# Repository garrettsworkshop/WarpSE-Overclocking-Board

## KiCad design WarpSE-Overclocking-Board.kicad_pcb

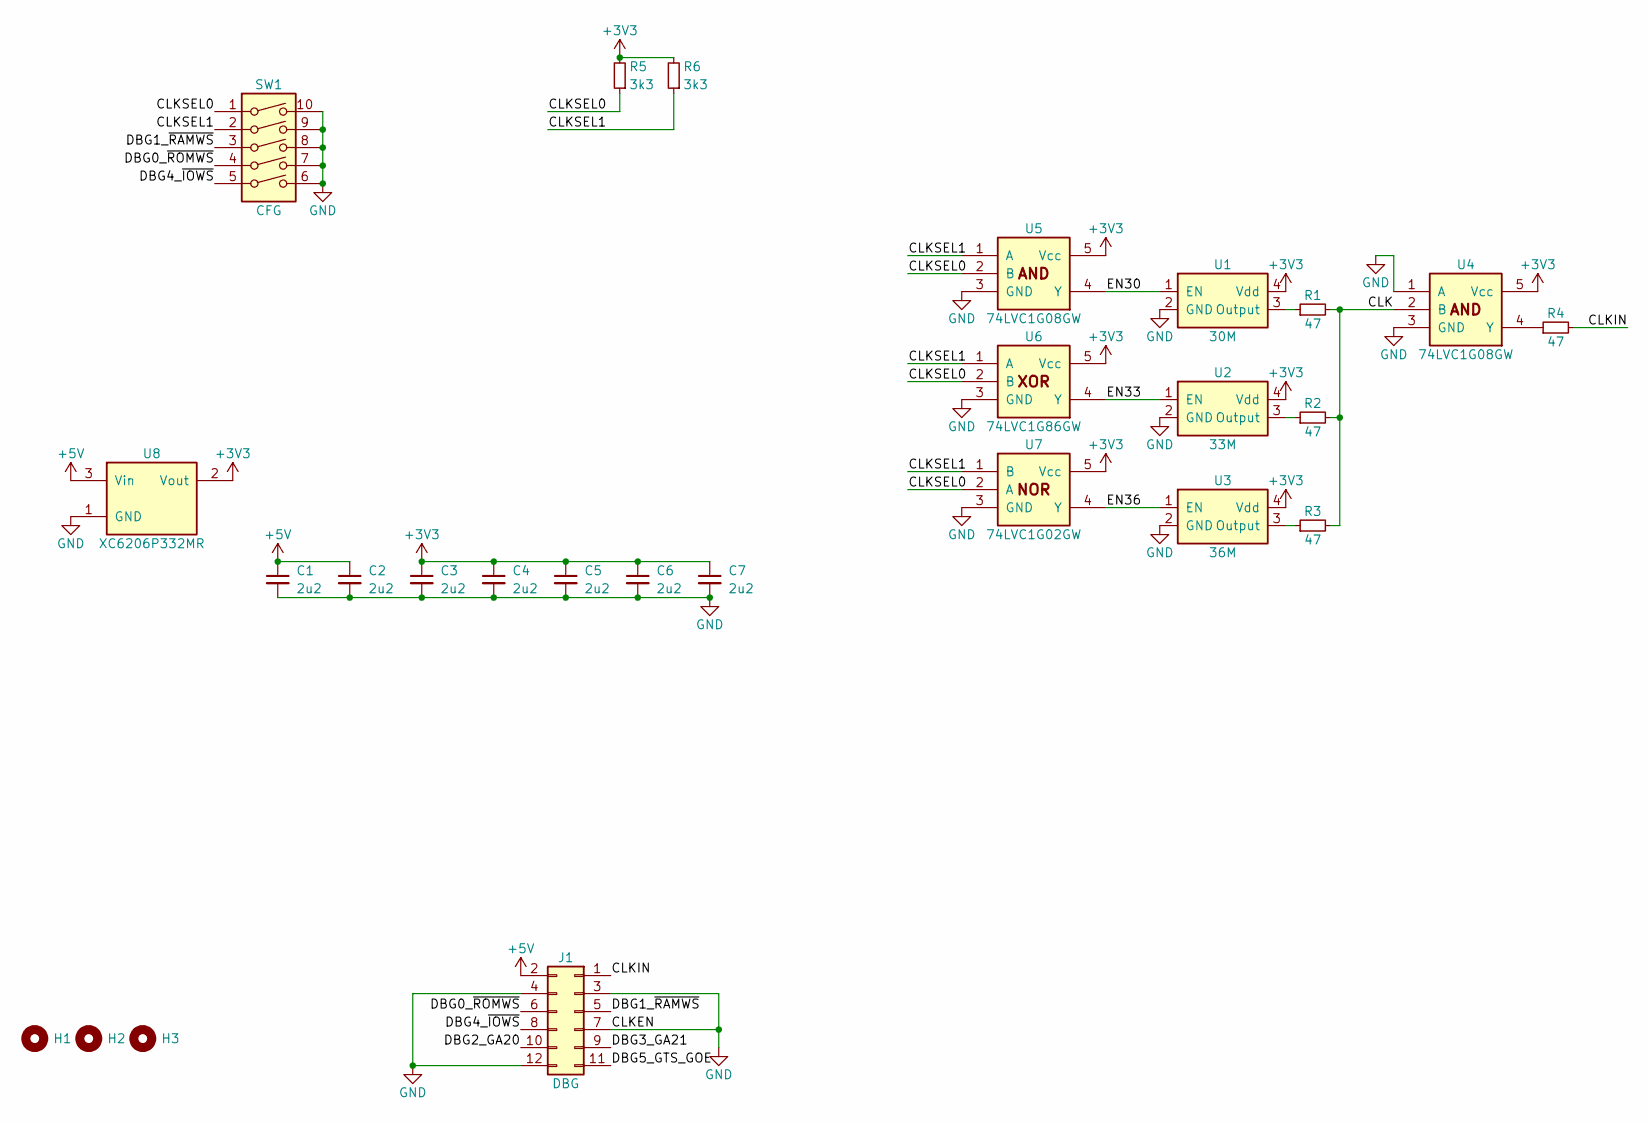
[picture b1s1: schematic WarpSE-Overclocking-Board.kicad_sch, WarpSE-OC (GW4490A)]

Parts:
C1, C2, C3, C4, C5, C6, C7: 2u2; C_0603; LCSC Part c23630
H1, H2, H3: PasteHole_1.152mm_NPTH
J1: DBG; PinHeader_2x06_P2.00mm_Vertical
R1, R2, R3, R4: 47; R_0603; LCSC Part C23182
R5, R6: 3k3; R_0603; LCSC Part C22978
SW1: CFG; SW_DIP_SPSTx05_Slide_DSHP05TS_P1.27mm; LCSC Part C2884836
U1: 30M; Crystal_SMD_3225-4Pin_3.2x2.5mm; LCSC Part C5179973
U2: 33M; Crystal_SMD_3225-4Pin_3.2x2.5mm; LCSC Part C5179975
U3: 36M; Crystal_SMD_3225-4Pin_3.2x2.5mm; LCSC Part C5179977
U4, U5: 74LVC1G08GW; SOT-353; LCSC Part C12512
U6: 74LVC1G86GW; SOT-353; LCSC Part C52350
U7: 74LVC1G02GW; SOT-353; LCSC Part C546692
U8: XC6206P332MR; SOT-23; LCSC Part C5446

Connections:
+3V3: C3.1, C4.1, C5.1, C6.1, C7.1, R5.2, R6.2, U1.4 (Vdd), U2.4 (Vdd), U3.4 (Vdd), U4.5 (Vcc), U5.5 (Vcc), U6.5 (Vcc), U7.5 (Vcc), U8.2 (Vout)
+5V: C1.1, C2.1, J1.2, U8.3 (Vin)
/CLK: R1.2, R2.2, R3.2, U4.2 (B)
/CLKIN: J1.1, R4.2
/CLKSEL0: R5.1, SW1.1, U5.2 (B), U6.2 (B), U7.2 (A)
/CLKSEL1: R6.1, SW1.2, U5.1 (A), U6.1 (A), U7.1 (B)
/DBG0_~ROMWS: J1.6, SW1.4
/DBG1_~RAMWS: J1.5, SW1.3
/DBG2_GA20: J1.10
/DBG3_GA21: J1.9
/DBG4_~IOWS: J1.8, SW1.5
/DBG5_GTS_GOE: J1.11
/EN30: U1.1 (EN), U5.4 (Y)
/EN33: U2.1 (EN), U6.4 (Y)
/EN36: U3.1 (EN), U7.4 (Y)
GND: C1.2, C2.2, C3.2, C4.2, C5.2, C6.2, C7.2, J1.3, J1.4, J1.7, J1.12, SW1.6, SW1.7, SW1.8, SW1.9, SW1.10, U1.2 (GND), U2.2 (GND), U3.2 (GND), U4.1 (A), U4.3 (GND), U5.3 (GND), U6.3 (GND), U7.3 (GND), U8.1 (GND)
unnamed: R1.1, U1.3 (Output)
unnamed: R2.1, U2.3 (Output)
unnamed: R3.1, U3.3 (Output)
unnamed: R4.1, U4.4 (Y)

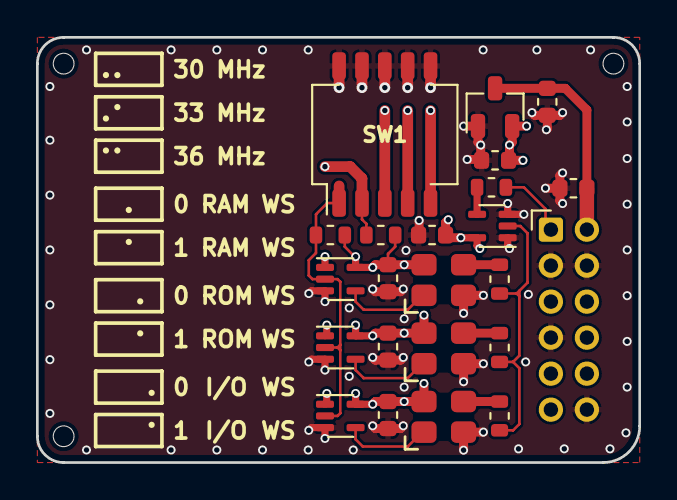
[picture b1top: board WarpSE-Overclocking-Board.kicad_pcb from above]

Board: 4 copper layers, 33.5 x 23.6 mm, 26 parts (0 on the bottom side), 17 nets.

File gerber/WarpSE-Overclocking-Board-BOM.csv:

"Reference","Quantity","Value","Footprint","LCSC Part","DNP"
"C1, C2, C3, C4, C5, C6, C7","7","2u2","stdpads:C_0603","c23630",""
"H1, H2, H3","3","~","stdpads:PasteHole_1.152mm_NPTH","",""
"J1","1","DBG","stdpads:PinHeader_2x06_P2.00mm_Vertical","",""
"R1, R2, R3, R4","4","47","stdpads:R_0603","C23182",""
"R5, R6","2","3k3","stdpads:R_0603","C22978",""
"SW1","1","CFG","stdpads:SW_DIP_SPSTx05_Slide_DSHP05TS_P1.27mm","C2884836",""
"U1","1","30M","stdpads:Crystal_SMD_3225-4Pin_3.2x2.5mm","C5179973",""
"U2","1","33M","stdpads:Crystal_SMD_3225-4Pin_3.2x2.5mm","C5179975",""
"U3","1","36M","stdpads:Crystal_SMD_3225-4Pin_3.2x2.5mm","C5179977",""
"U4, U5","2","74LVC1G08GW","stdpads:SOT-353","C12512",""
"U6","1","74LVC1G86GW","stdpads:SOT-353","C52350",""
"U7","1","74LVC1G02GW","stdpads:SOT-353","C546692",""
"U8","1","XC6206P332MR","stdpads:SOT-23","C5446",""

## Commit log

2024-10-22 Add overclocking board
2025-03-30 As sent to JLC
